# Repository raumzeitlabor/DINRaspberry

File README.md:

This is a simple raspberry pi adapter to DIN 41612 (Hirschmann Backplane)

Also has a separate USB connector (optional fit) in case of excess power usage via the ribbon cable or additional power requirements for connected USB devices.

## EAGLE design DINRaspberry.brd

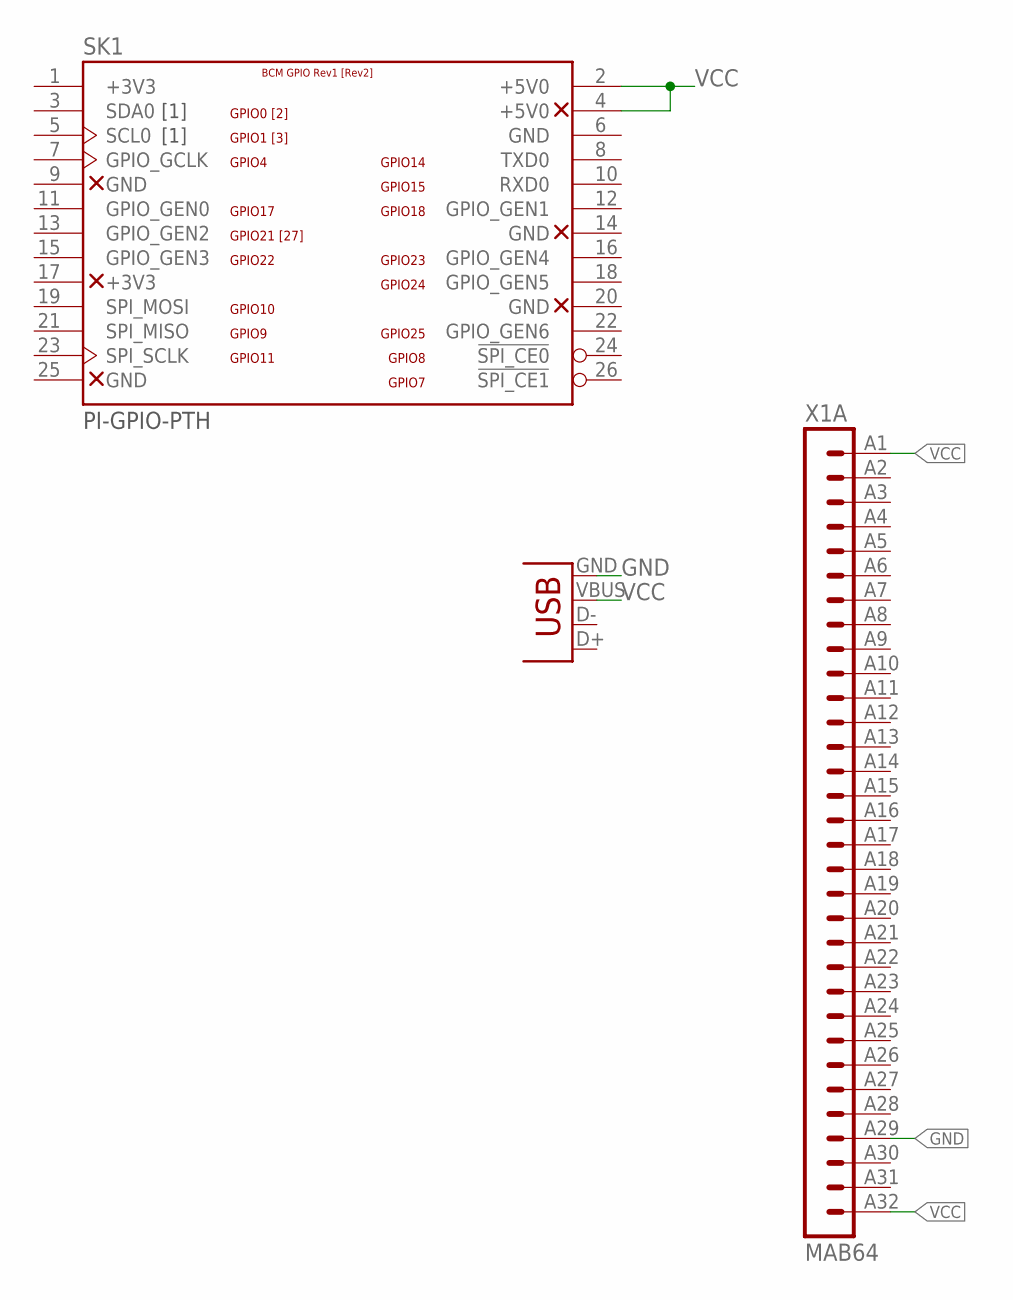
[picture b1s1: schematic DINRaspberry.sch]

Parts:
SK1: PI-GPIO-PTH; GPIO-CONNECTOR
X1: MAB64
X2: USBPTH; USB-B-PTH

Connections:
+3V3: SK1.1 (+3V3)
GND: SK1.6 (GND), X1.A29 (29), X2.GND
VCC: SK1.2 (+5V0), SK1.4 (+5V0), X1.A1 (1), X1.A32 (32), X2.VBUS

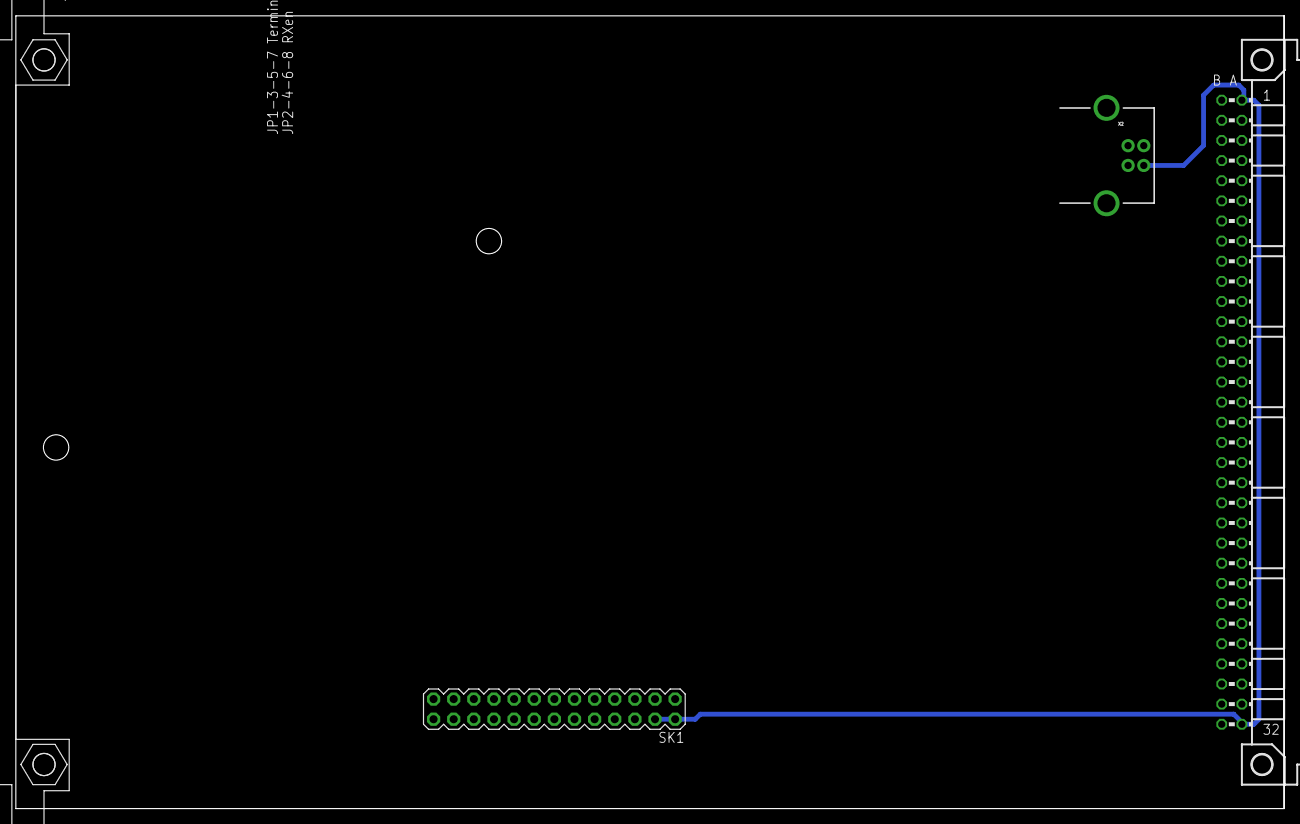
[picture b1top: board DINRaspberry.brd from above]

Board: 2 copper layers, 160.0 x 100.0 mm, 4 parts (0 on the bottom side), 2 nets.

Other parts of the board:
U$6: EK-FP

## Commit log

2013-11-29 Added nice pcb pics

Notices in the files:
parts and their libraries:
SparkFun: Licensing: CC v3.0 Share-Alike You are welcome to use this library for commercial purposes.
